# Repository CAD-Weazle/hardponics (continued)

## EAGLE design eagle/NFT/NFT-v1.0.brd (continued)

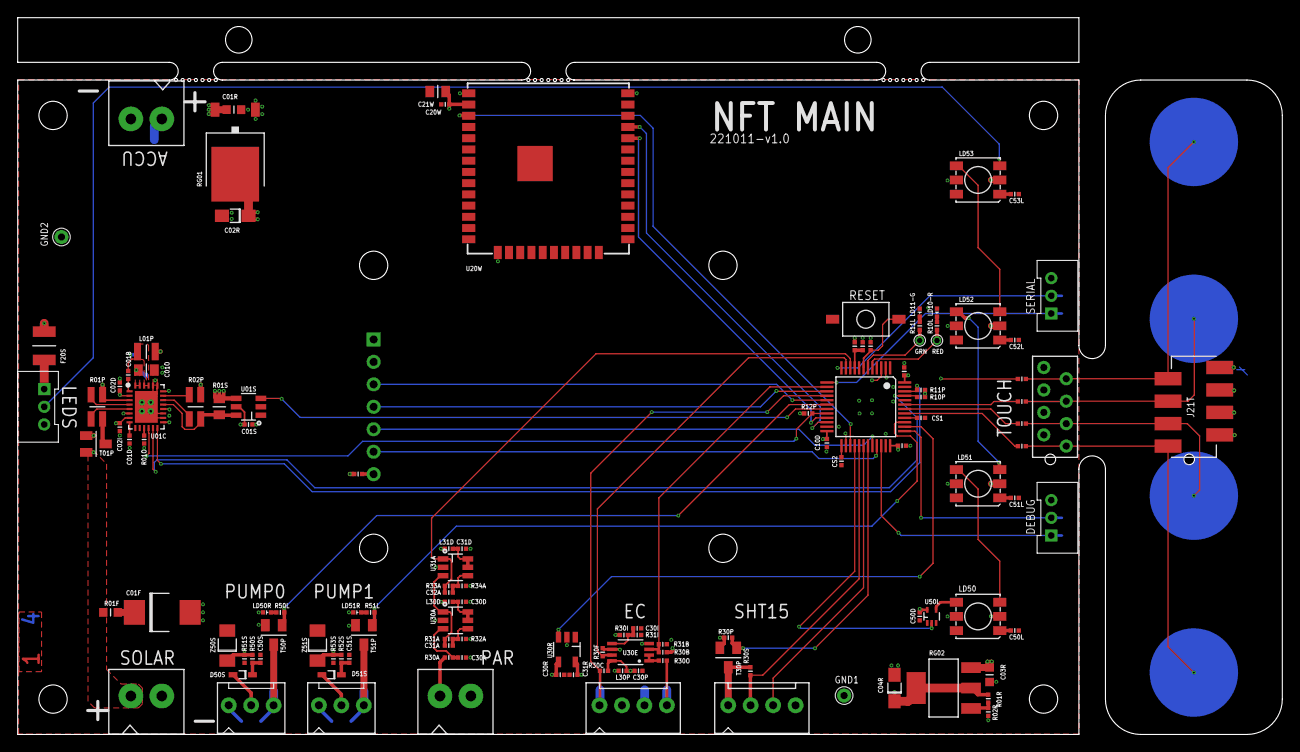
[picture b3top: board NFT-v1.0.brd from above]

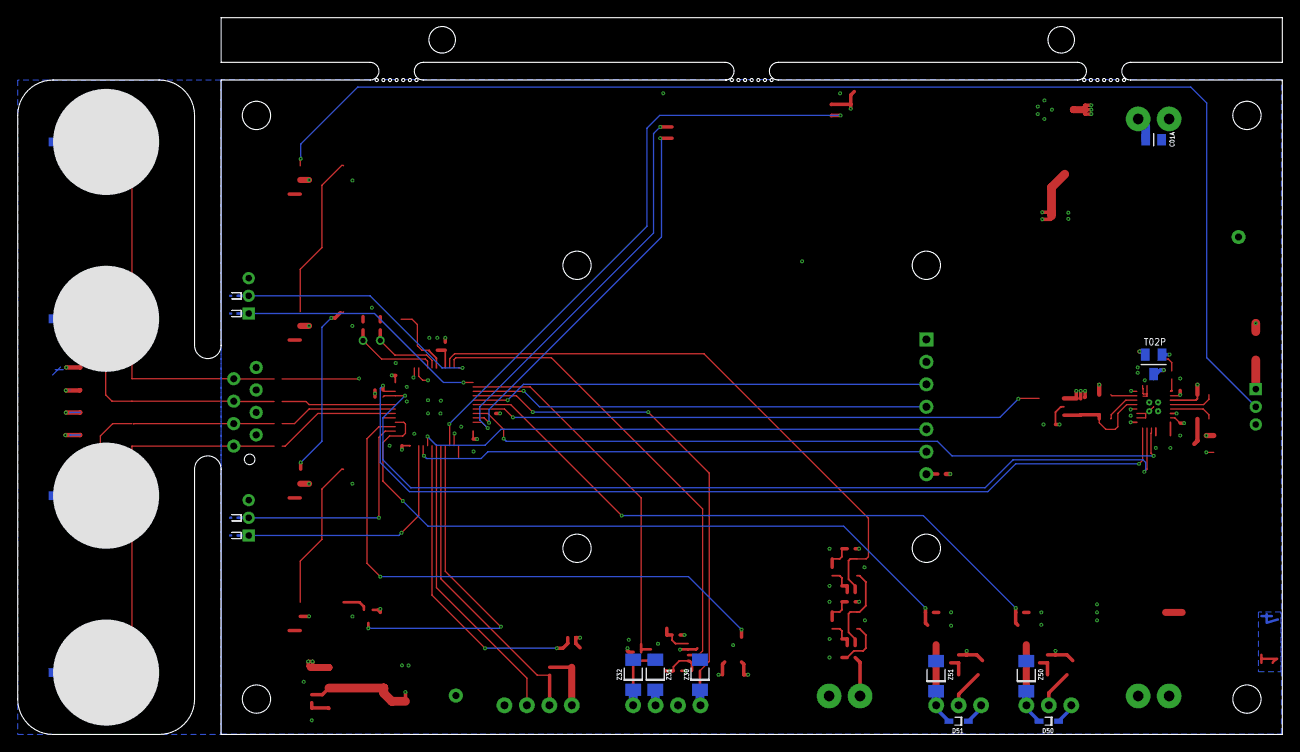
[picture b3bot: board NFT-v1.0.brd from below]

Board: 4 copper layers, 143.0 x 81.0 mm, 150 parts (17 on the bottom side), 99 nets.

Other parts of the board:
U$132, U$133, U$134: EC_MOUSEBITES
U$136, U$137: EC_TOOL-REGISTRATION

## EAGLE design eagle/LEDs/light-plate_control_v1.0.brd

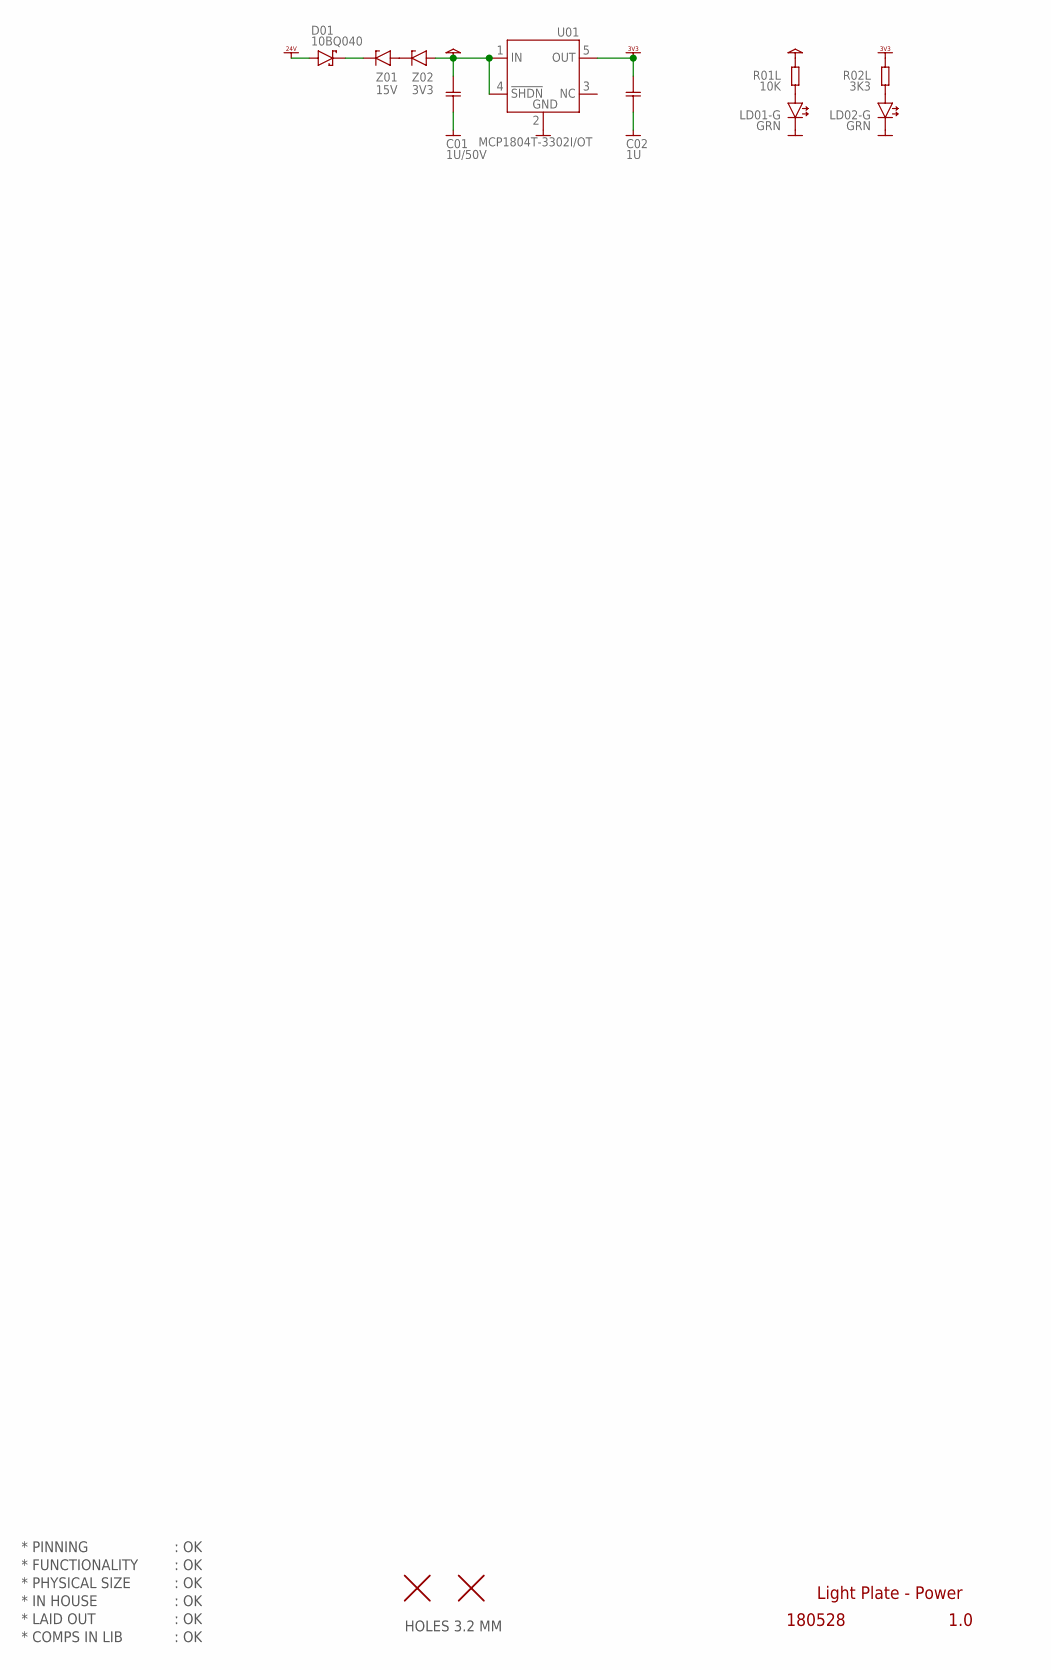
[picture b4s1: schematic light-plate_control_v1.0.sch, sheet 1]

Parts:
C01: 1U/50V; CAP0603
C02: 1U; CAP0603
D01: 10BQ040; DIODE_SMA
H2, H3: HOLE_NPTH_3.2MM
LD01-G, LD02-G: GRN; LED_SMD_0603
R01L: 10K; RES0603
R02L: 3K3; RES0603
U01: MCP1804T-3302I/OT; SOT23-5
Z01: 15V; ZENER_SOD80
Z02: 3V3; ZENER_SOD80

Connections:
GND: C01.2, C02.2, LD01-G.C, LD02-G.C, U01.2 (2.GND); also elsewhere on the board
unnamed: LD02-G.A, R02L.2
unnamed: LD01-G.A, R01L.2
unnamed: D01.C (-), Z01.2 (-)
unnamed: Z01.1 (+), Z02.2 (-)
VCC: C01.1, R01L.1, U01.1 (1.IN), U01.4 (4.SHDN), Z02.1 (+)
VDD_3V3: C02.1, R02L.1, U01.5 (5.OUT); also elsewhere on the board
VDD_24V: D01.A (+); also elsewhere on the board

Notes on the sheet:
* PINNING
* FUNCTIONALITY
* PHYSICAL SIZE
* LAID OUT
* COMPS IN LIB
* IN HOUSE
HOLES 3.2 MM
Light Plate - Power
180528
1.0
: OK

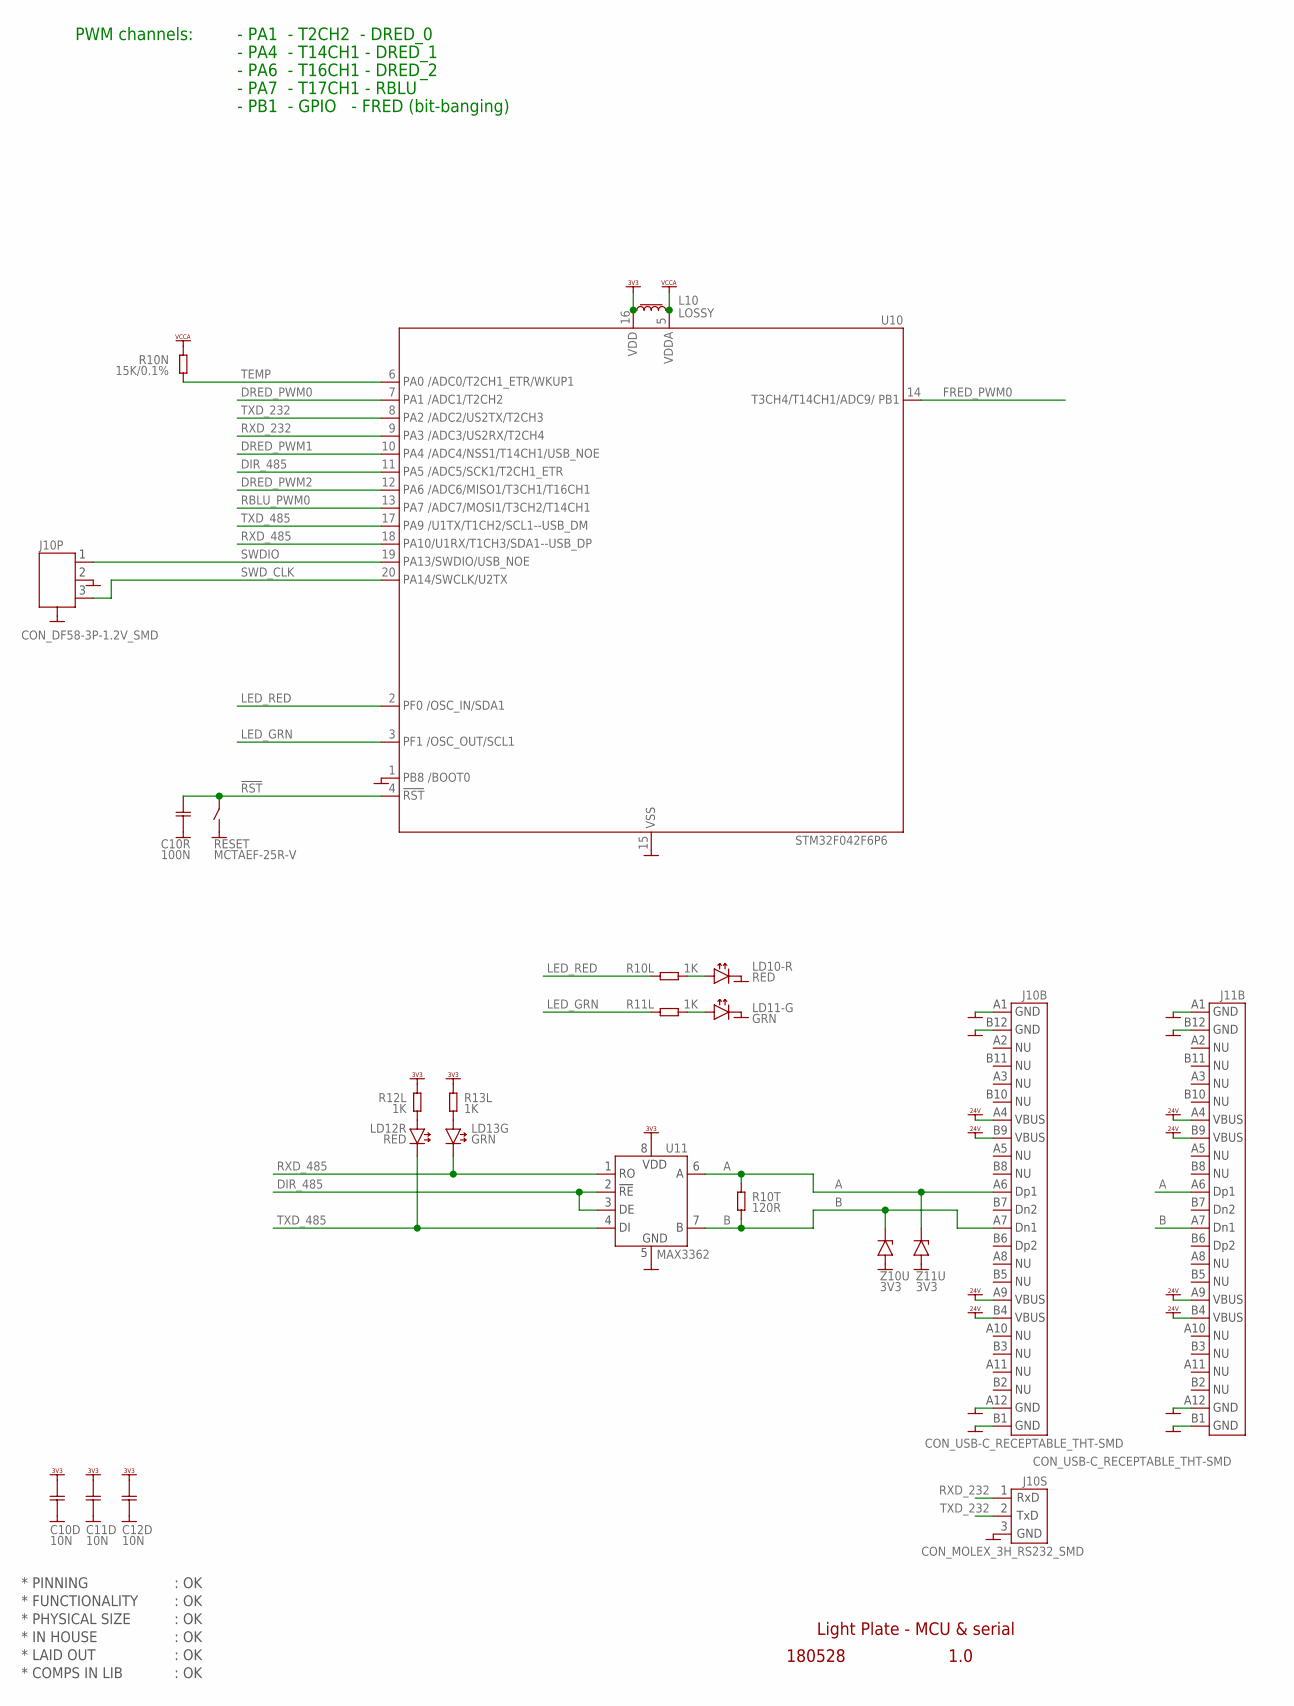
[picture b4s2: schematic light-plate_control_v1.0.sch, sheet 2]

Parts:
C10D, C11D, C12D: 10N; CAP0603
C10R: 100N; CAP0603
J10B, J11B: CON_USB-C_RECEPTABLE_THT-SMD
J10P: CON_DF58-3P-1.2V_SMD
J10S: CON_MOLEX_3H_RS232_SMD; CON_MOLEX_3H+SMD
L10: LOSSY; L_0603
LD10-R, LD12R: RED; LED_SMD_0603
LD11-G, LD13G: GRN; LED_SMD_0603
R10L, R11L, R12L, R13L: 1K; RES0603
R10N: 15K/0.1%; RES0603
R10T: 120R; RES0603
RESET: MCTAEF-25R-V; SWITCH_SMD_PBUTTON_2P
U10: STM32F042F6P6; TSSOP20
U11: MAX3362; SOT23-8
Z10U, Z11U: 3V3; ZENER_SOD80

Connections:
!RST: C10R.1, RESET.2 (3-4), U10.4 (4.!RST)
A: J10B.A6 (A6.DP1), J11B.A6 (A6.DP1), R10T.1, U11.6 (6.A), Z11U.2 (-)
B: J10B.A7 (A7.DN1), J11B.A7 (A7.DN1), R10T.2, U11.7 (7.B), Z10U.2 (-)
DIR_485: U10.11 (11.PA5), U11.2 (2.!RE), U11.3 (3.DE)
DRED_PWM0: U10.7 (7.PA1); also elsewhere on the board
DRED_PWM1: U10.10 (10.PA4); also elsewhere on the board
DRED_PWM2: U10.12 (12.PA6); also elsewhere on the board
FRED_PWM0: U10.14 (14.PB1); also elsewhere on the board
GND: C10D.2, C10R.2, C11D.2, C12D.2, J10B.A1 (A1.GND), J10B.A12 (A12.GND), J10B.B1 (B1.GND), J10B.B12 (B12.GND), J10P.2, J10P.GND1 (4), J10P.GND2 (4), J10S.3, J11B.A1 (A1.GND), J11B.A12 (A12.GND), J11B.B1 (B1.GND), J11B.B12 (B12.GND), LD10-R.C, LD11-G.C, RESET.1 (1-2), U10.1 (1.BOOT0), U10.15 (15.GND), U11.5 (5.GND), Z10U.1 (+), Z11U.1 (+); also elsewhere on the board
LED_GRN: R11L.1, U10.3 (3.OSC_OUT)
LED_RED: R10L.1, U10.2 (2.OSC_IN)
unnamed: LD11-G.A, R11L.2
unnamed: LD10-R.A, R10L.2
unnamed: LD13G.A, R13L.2
unnamed: LD12R.A, R12L.2
RBLU_PWM0: U10.13 (13.PA7); also elsewhere on the board
RXD_232: J10S.1, U10.9 (9.PA3)
RXD_485: LD13G.C, U10.18 (18.PA10), U11.1 (1.RO)
SWDIO: J10P.1, U10.19 (19.PA13)
SWD_CLK: J10P.3, U10.20 (20.PA14)
TEMP: R10N.1, U10.6 (6.PA0)
TXD_232: J10S.2, U10.8 (8.PA2)
TXD_485: LD12R.C, U10.17 (17.PA9), U11.4 (4.DI)
VCCA: L10.2, R10N.2, U10.5 (5.VDDA)
VDD_3V3: C10D.1, C11D.1, C12D.1, L10.1, R12L.1, R13L.1, U10.16 (16.VDD), U11.8 (8.VDD); also elsewhere on the board
VDD_24V: J10B.A4 (A4.VBUS), J10B.A9 (A9.VBUS), J10B.B4 (B4.VBUS), J10B.B9 (B9.VBUS), J11B.A4 (A4.VBUS), J11B.A9 (A9.VBUS), J11B.B4 (B4.VBUS), J11B.B9 (B9.VBUS); also elsewhere on the board

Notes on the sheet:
* PINNING
* FUNCTIONALITY
* PHYSICAL SIZE
* LAID OUT
* COMPS IN LIB
* IN HOUSE
: OK
Light Plate - MCU & serial
180528
1.0
PWM channels:
- PA1 - T2CH2 - DRED_0
- PA4 - T14CH1 - DRED_1
- PA6 - T16CH1 - DRED_2
- PA7 - T17CH1 - RBLU
- PB1 - GPIO - FRED (bit-banging)

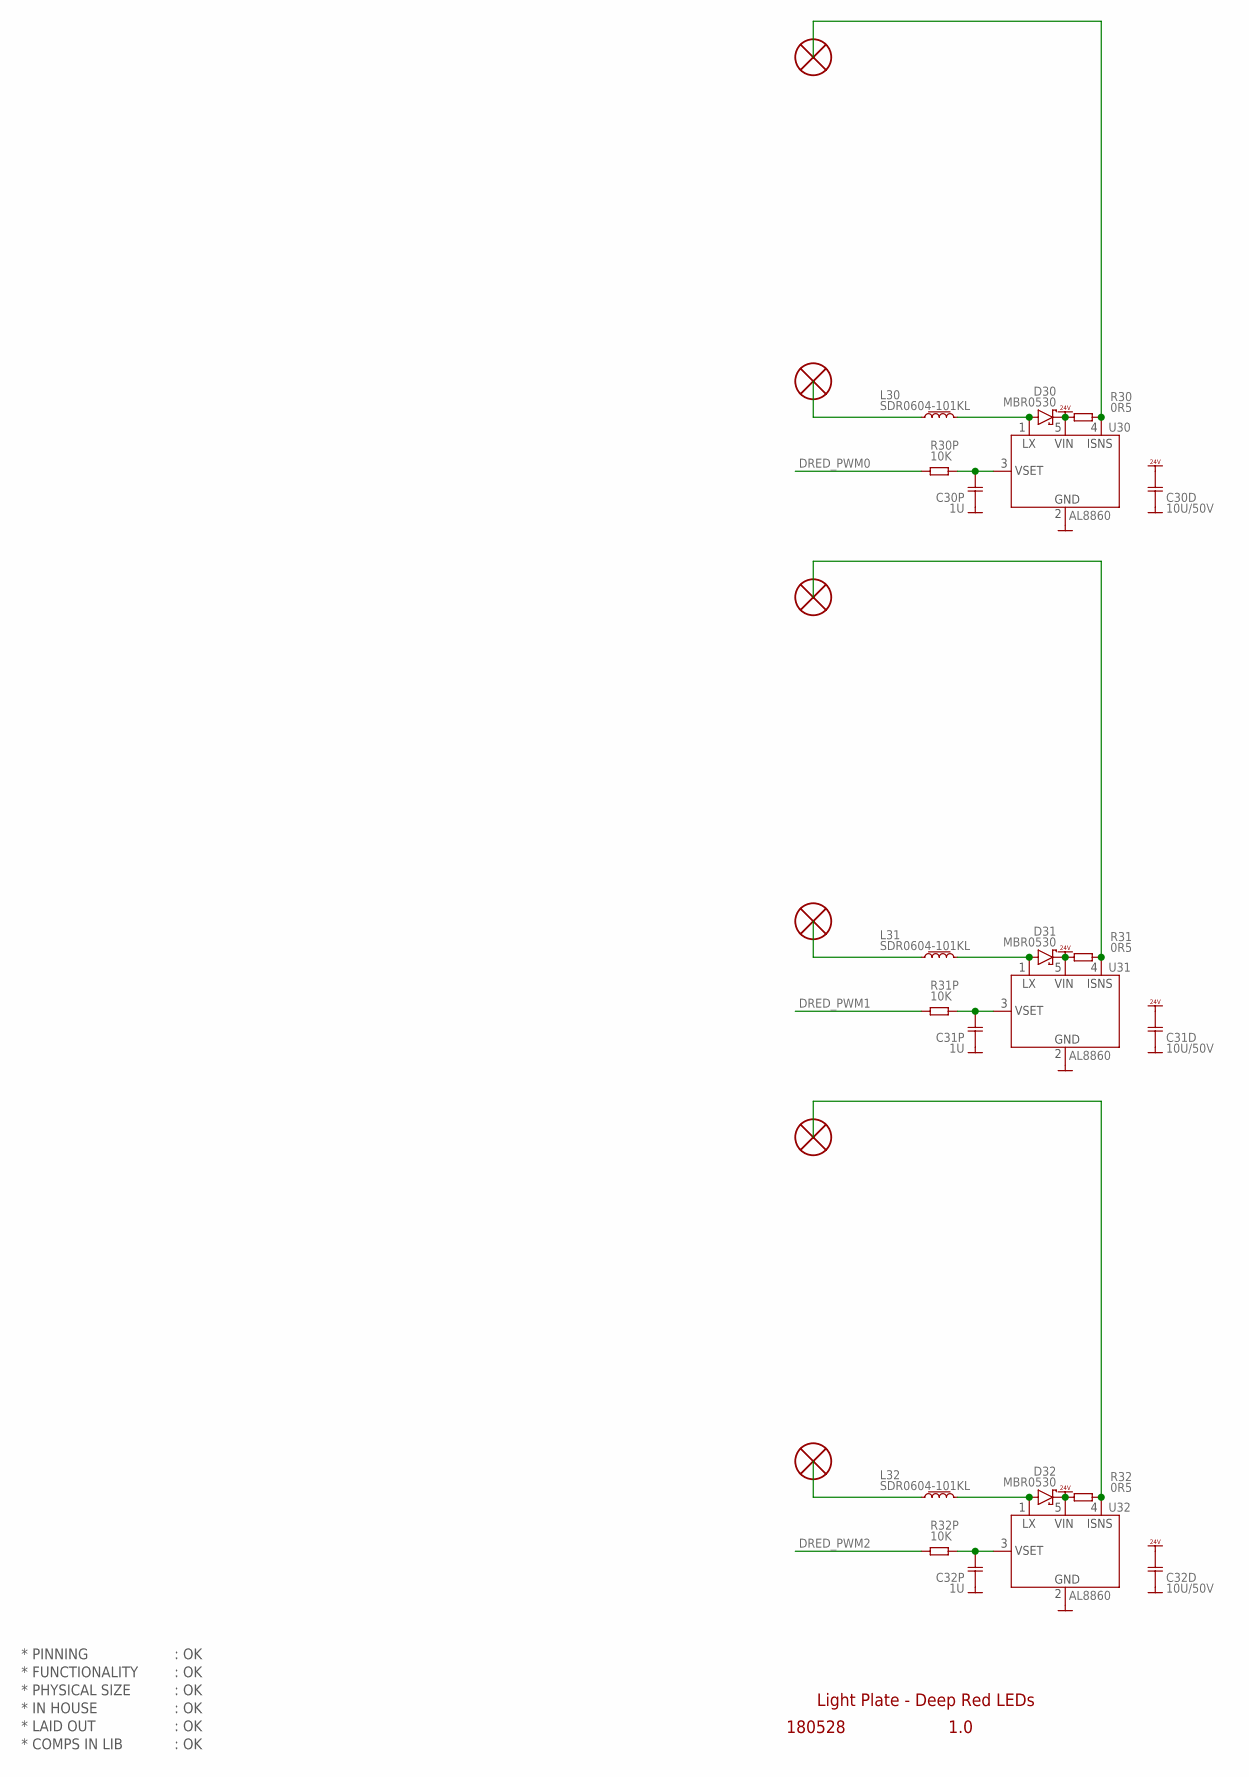
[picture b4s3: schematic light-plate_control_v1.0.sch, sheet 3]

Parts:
C30D, C31D, C32D: 10U/50V; CAP0603
C30P, C31P, C32P: 1U; CAP0603
D30, D31, D32: MBR0530; DIODE_SOD123
H5, H6, H7, H8, H9, H10: HOLE_PTH_1.0MM
L30, L31, L32: SDR0604-101KL; L_SDR0604
R30, R31, R32: 0R5; RES0603
R30P, R31P, R32P: 10K; RES0603
U30, U31, U32: AL8860; SOT23-5

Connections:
DRED_PWM0: R30P.1; also elsewhere on the board
DRED_PWM1: R31P.1; also elsewhere on the board
DRED_PWM2: R32P.1; also elsewhere on the board
GND: C30D.2, C30P.2, C31D.2, C31P.2, C32D.2, C32P.2, U30.2 (2.GND), U31.2 (2.GND), U32.2 (2.GND); also elsewhere on the board
unnamed: C30P.1, R30P.2, U30.3 (3.VSET)
unnamed: H5.1, L30.1
unnamed: H8.1, R31.2, U31.4 (4.ISENSE)
unnamed: D30.2 (+), L30.2, U30.1 (1.LX)
unnamed: H6.1, R30.2, U30.4 (4.ISENSE)
unnamed: H7.1, L31.1
unnamed: H10.1, R32.2, U32.4 (4.ISENSE)
unnamed: H9.1, L32.1
unnamed: D31.2 (+), L31.2, U31.1 (1.LX)
unnamed: C31P.1, R31P.2, U31.3 (3.VSET)
unnamed: D32.2 (+), L32.2, U32.1 (1.LX)
unnamed: C32P.1, R32P.2, U32.3 (3.VSET)
VDD_24V: C30D.1, C31D.1, C32D.1, D30.1- (-), D31.1- (-), D32.1- (-), R30.1, R31.1, R32.1, U30.5 (5.VIN), U31.5 (5.VIN), U32.5 (5.VIN); also elsewhere on the board

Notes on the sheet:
* PINNING
* FUNCTIONALITY
* PHYSICAL SIZE
* LAID OUT
* COMPS IN LIB
* IN HOUSE
: OK
Light Plate - Deep Red LEDs
1.0
180528

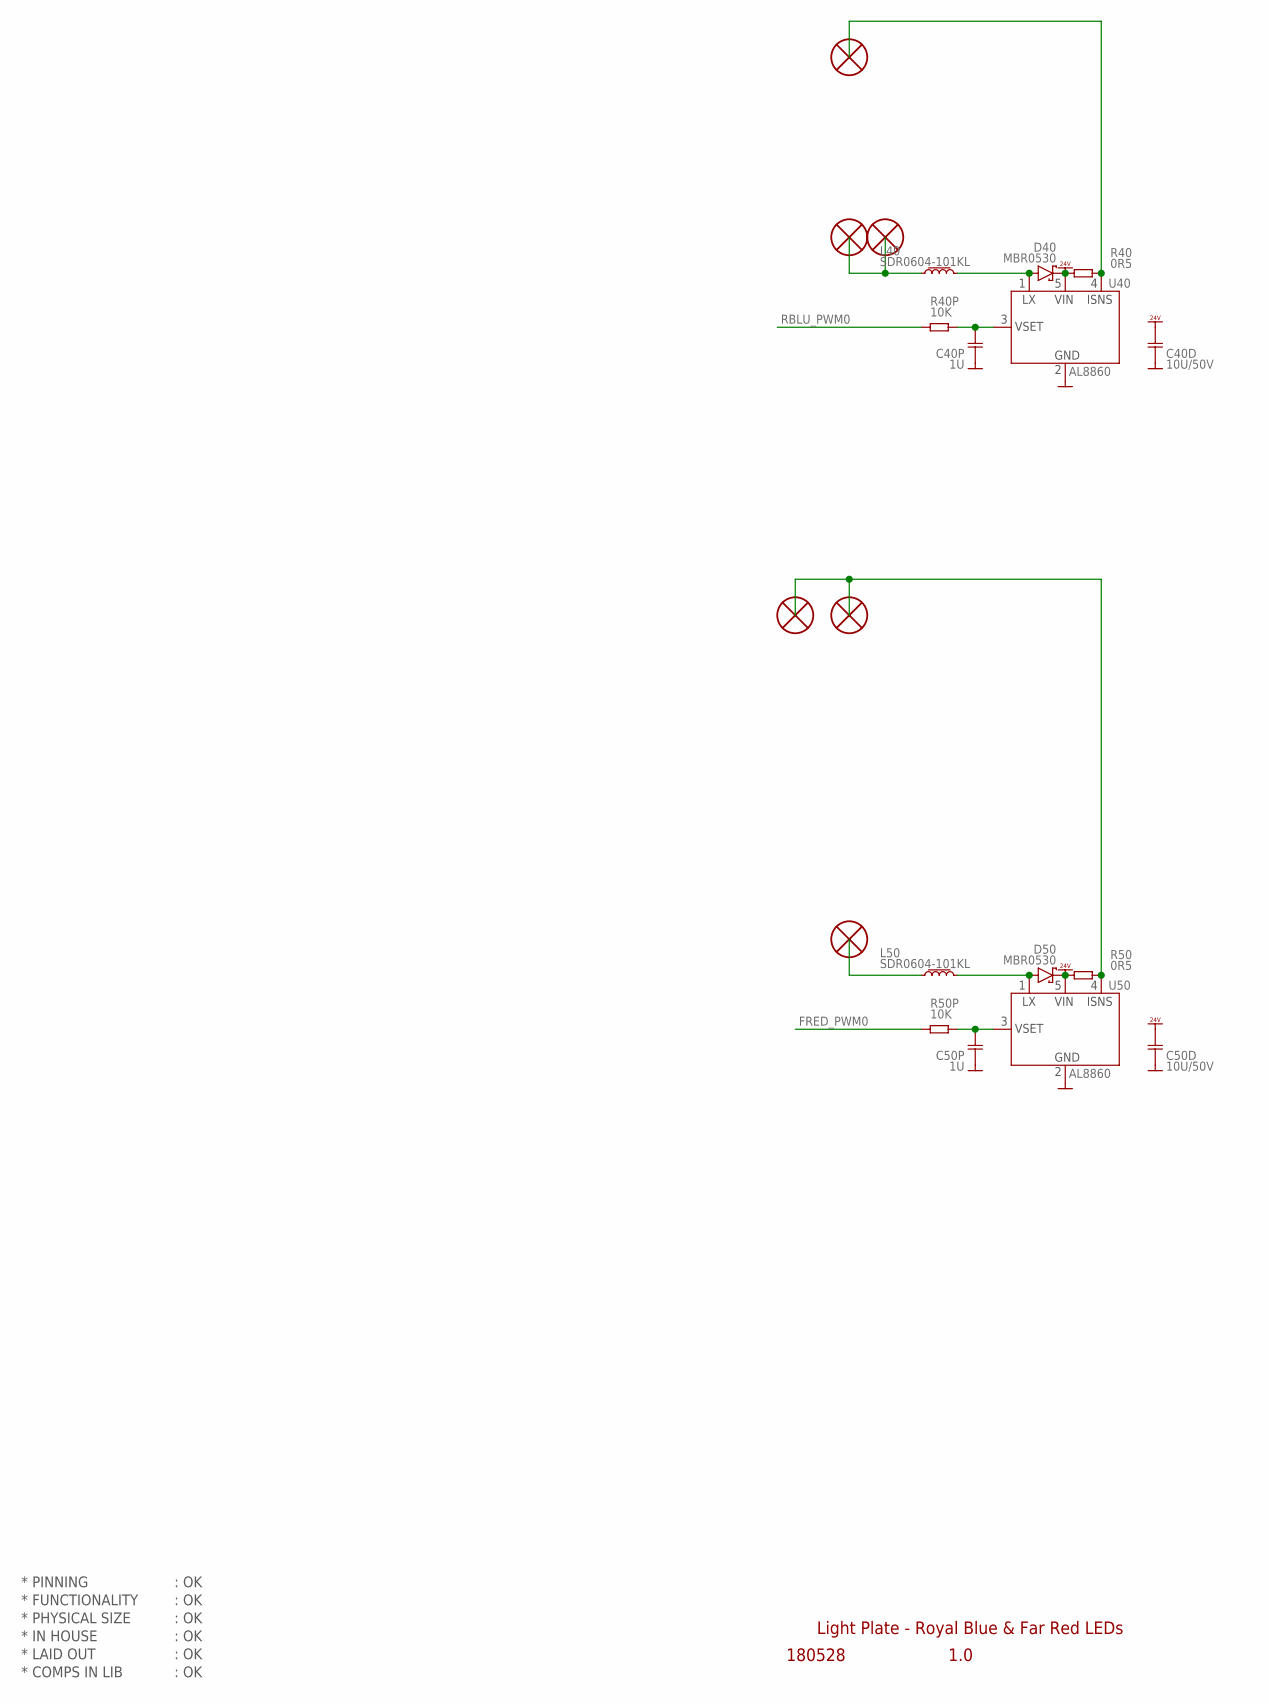
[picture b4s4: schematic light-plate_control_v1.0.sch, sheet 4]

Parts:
C40D, C50D: 10U/50V; CAP0603
C40P, C50P: 1U; CAP0603
D40, D50: MBR0530; DIODE_SOD123
H11, H12, H13, H14, H15, H16: HOLE_PTH_1.0MM
L40, L50: SDR0604-101KL; L_SDR0604
R40, R50: 0R5; RES0603
R40P, R50P: 10K; RES0603
U40, U50: AL8860; SOT23-5

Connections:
FRED_PWM0: R50P.1; also elsewhere on the board
GND: C40D.2, C40P.2, C50D.2, C50P.2, U40.2 (2.GND), U50.2 (2.GND); also elsewhere on the board
unnamed: H11.1, H15.1, L40.1
unnamed: H12.1, R40.2, U40.4 (4.ISENSE)
unnamed: H14.1, H16.1, R50.2, U50.4 (4.ISENSE)
unnamed: D50.2 (+), L50.2, U50.1 (1.LX)
unnamed: C50P.1, R50P.2, U50.3 (3.VSET)
unnamed: H13.1, L50.1
unnamed: D40.2 (+), L40.2, U40.1 (1.LX)
unnamed: C40P.1, R40P.2, U40.3 (3.VSET)
RBLU_PWM0: R40P.1; also elsewhere on the board
VDD_24V: C40D.1, C50D.1, D40.1- (-), D50.1- (-), R40.1, R50.1, U40.5 (5.VIN), U50.5 (5.VIN); also elsewhere on the board

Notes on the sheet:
* PINNING
* FUNCTIONALITY
* PHYSICAL SIZE
* LAID OUT
* COMPS IN LIB
* IN HOUSE
: OK
Light Plate - Royal Blue & Far Red LEDs
1.0
180528

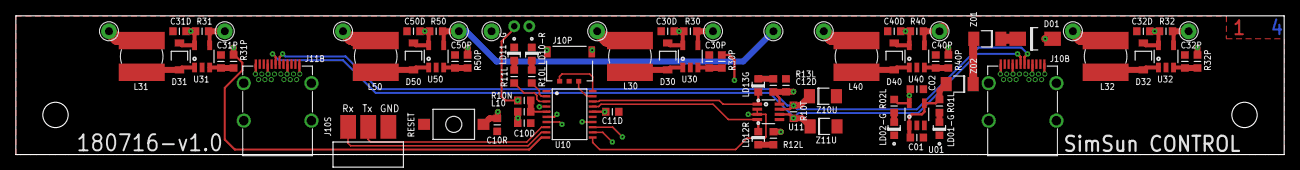
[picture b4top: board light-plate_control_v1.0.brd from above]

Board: 4 copper layers, 160.0 x 17.5 mm, 83 parts (0 on the bottom side), 51 nets.

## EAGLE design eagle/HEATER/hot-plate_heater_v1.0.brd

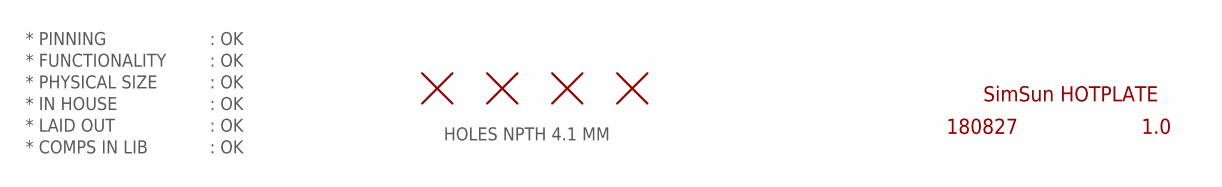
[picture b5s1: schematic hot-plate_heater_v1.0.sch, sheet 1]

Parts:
H1, H2, H3, H4: HOLE_NPTH_4.1MM

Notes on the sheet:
* PINNING
* FUNCTIONALITY
* PHYSICAL SIZE
* LAID OUT
* COMPS IN LIB
* IN HOUSE
HOLES NPTH 4.1 MM
SimSun HOTPLATE
180827
1.0
: OK

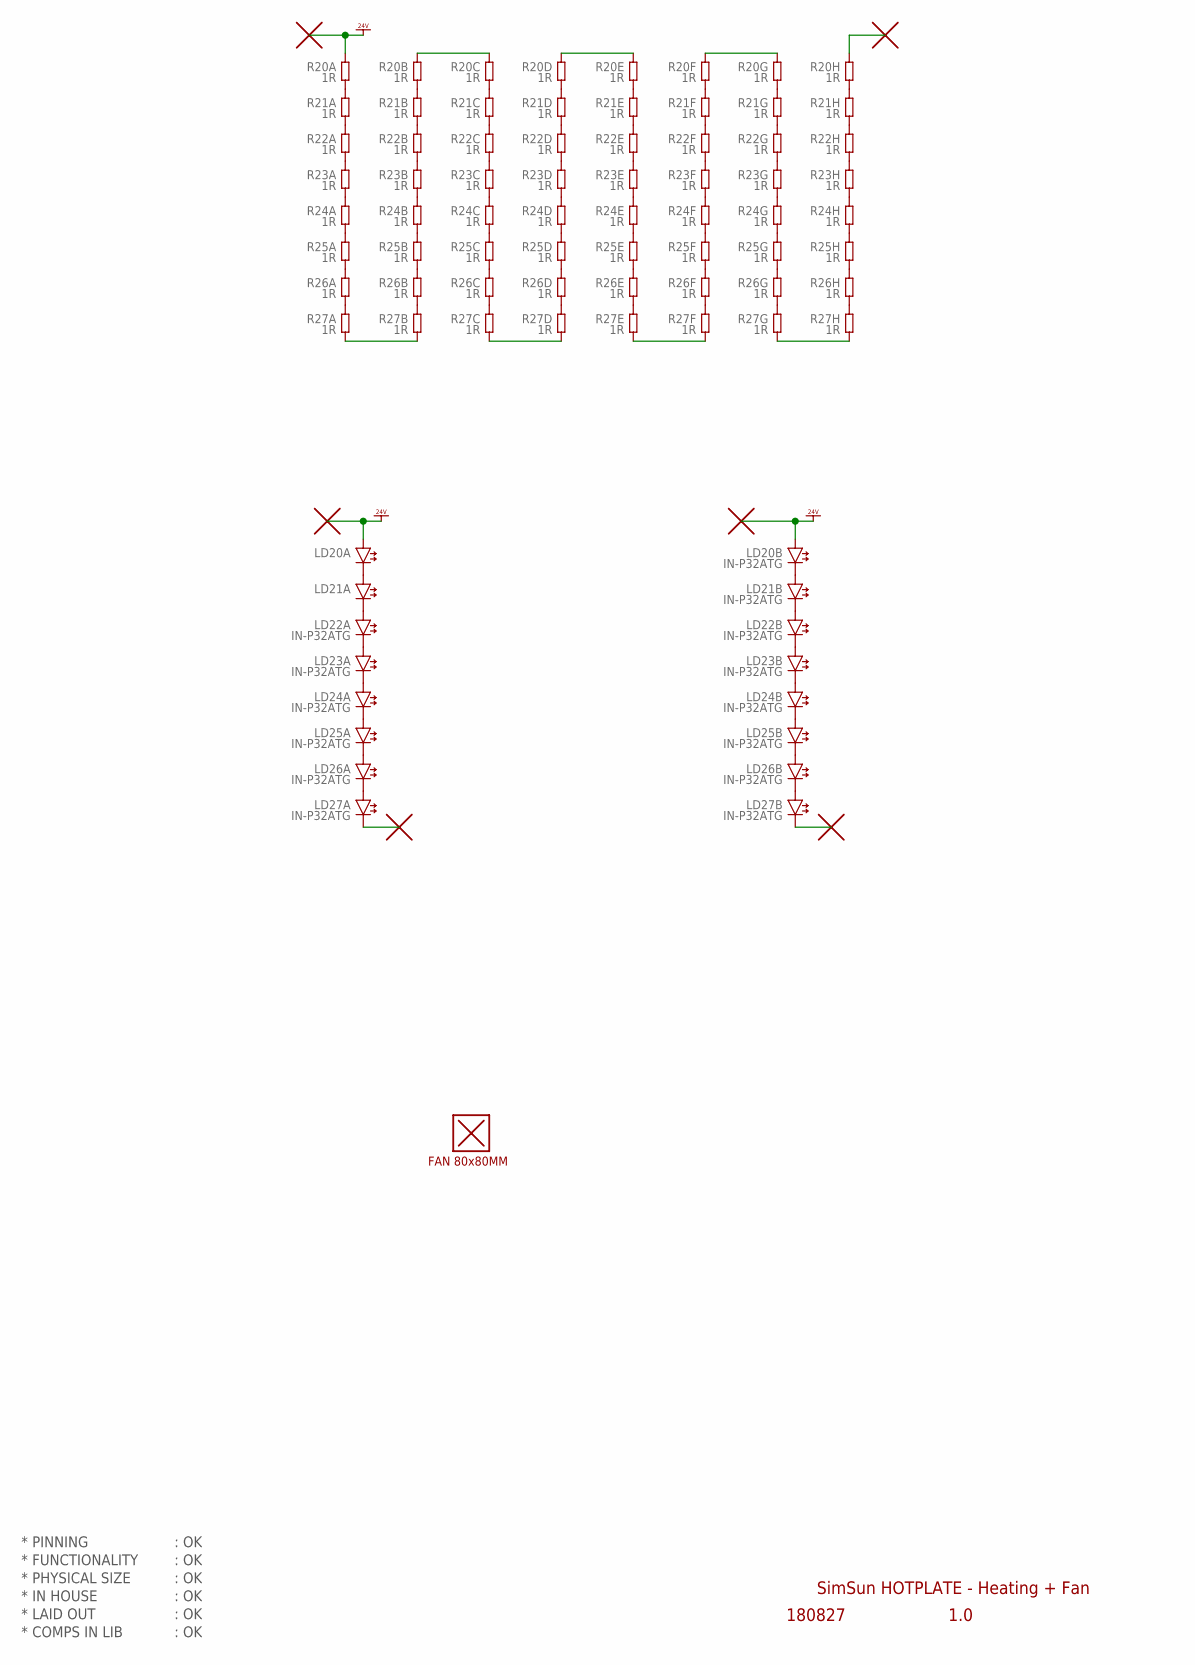
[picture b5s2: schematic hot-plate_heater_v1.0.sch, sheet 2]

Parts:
H9: FAN_80X80MM_SANYO_SANACE80
H18, H19, H20, H21, H22, H23: PAD_ROUND_3.2MM
LD20A, LD20B, LD21A, LD21B, LD22A, LD22B, LD23A, LD23B, LD24A, LD24B, LD25A, LD25B, LD26A, LD26B, LD27A, LD27B: IN-P32ATG; LED_SMD_PLCC2
R20A, R20B, R20C, R20D, R20E, R20F, R20G, R20H, R21A, R21B, R21C, R21D, R21E, R21F, R21G, R21H, R22A, R22B, R22C, R22D, R22E, R22F, R22G, R22H, R23A, R23B, R23C, R23D, R23E, R23F, R23G, R23H, R24A, R24B, R24C, R24D, R24E, R24F, R24G, R24H, R25A, R25B, R25C, R25D, R25E, R25F, R25G, R25H, R26A, R26B, R26C, R26D, R26E, R26F, R26G, R26H, R27A, R27B, R27C, R27D, R27E, R27F, R27G, R27H: 1R; RES2512

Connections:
unnamed: H19.P, R20H.1
unnamed: R20A.2, R21A.1
unnamed: R21A.2, R22A.1
unnamed: R22A.2, R23A.1
unnamed: R23A.2, R24A.1
unnamed: R24A.2, R25A.1
unnamed: R25A.2, R26A.1
unnamed: R26A.2, R27A.1
unnamed: R20B.2, R21B.1
unnamed: R21B.2, R22B.1
unnamed: R22B.2, R23B.1
unnamed: R23B.2, R24B.1
unnamed: R24B.2, R25B.1
unnamed: R25B.2, R26B.1
unnamed: R26B.2, R27B.1
unnamed: R27A.2, R27B.2
unnamed: R20C.2, R21C.1
unnamed: R21C.2, R22C.1
unnamed: R22C.2, R23C.1
unnamed: R23C.2, R24C.1
unnamed: R24C.2, R25C.1
unnamed: R25C.2, R26C.1
unnamed: R26C.2, R27C.1
unnamed: R20B.1, R20C.1
unnamed: R20D.2, R21D.1
unnamed: R21D.2, R22D.1
unnamed: R22D.2, R23D.1
unnamed: R23D.2, R24D.1
unnamed: R24D.2, R25D.1
unnamed: R25D.2, R26D.1
unnamed: R26D.2, R27D.1
unnamed: R27C.2, R27D.2
unnamed: R20E.2, R21E.1
unnamed: R21E.2, R22E.1
unnamed: R22E.2, R23E.1
unnamed: R23E.2, R24E.1
unnamed: R24E.2, R25E.1
unnamed: R25E.2, R26E.1
unnamed: R26E.2, R27E.1
unnamed: R20D.1, R20E.1
unnamed: R20F.2, R21F.1
unnamed: R21F.2, R22F.1
unnamed: R22F.2, R23F.1
unnamed: R23F.2, R24F.1
unnamed: R24F.2, R25F.1
unnamed: R25F.2, R26F.1
unnamed: R26F.2, R27F.1
unnamed: R27E.2, R27F.2
unnamed: R20G.2, R21G.1
unnamed: R21G.2, R22G.1
unnamed: R22G.2, R23G.1
unnamed: R23G.2, R24G.1
unnamed: R24G.2, R25G.1
unnamed: R25G.2, R26G.1
unnamed: R26G.2, R27G.1
unnamed: R20F.1, R20G.1
unnamed: R20H.2, R21H.1
unnamed: R21H.2, R22H.1
unnamed: R22H.2, R23H.1
unnamed: R23H.2, R24H.1
unnamed: R24H.2, R25H.1
unnamed: R25H.2, R26H.1
unnamed: R26H.2, R27H.1
unnamed: R27G.2, R27H.2
unnamed: LD20A.C (-), LD21A.A (+)
unnamed: LD21A.C (-), LD22A.A (+)
unnamed: LD22A.C (-), LD23A.A (+)
unnamed: LD23A.C (-), LD24A.A (+)
unnamed: LD24A.C (-), LD25A.A (+)
unnamed: LD25A.C (-), LD26A.A (+)
unnamed: LD20B.C (-), LD21B.A (+)
unnamed: LD21B.C (-), LD22B.A (+)
unnamed: LD22B.C (-), LD23B.A (+)
unnamed: LD23B.C (-), LD24B.A (+)
unnamed: LD24B.C (-), LD25B.A (+)
unnamed: LD25B.C (-), LD26B.A (+)
unnamed: LD26A.C (-), LD27A.A (+)
unnamed: LD26B.C (-), LD27B.A (+)
unnamed: H23.P, LD27B.C (-)
unnamed: H22.P, LD27A.C (-)
VDD_24V: H18.P, H20.P, H21.P, LD20A.A (+), LD20B.A (+), R20A.1

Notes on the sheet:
* PINNING
* FUNCTIONALITY
* PHYSICAL SIZE
* LAID OUT
* COMPS IN LIB
* IN HOUSE
: OK
SimSun HOTPLATE - Heating + Fan
1.0
180827

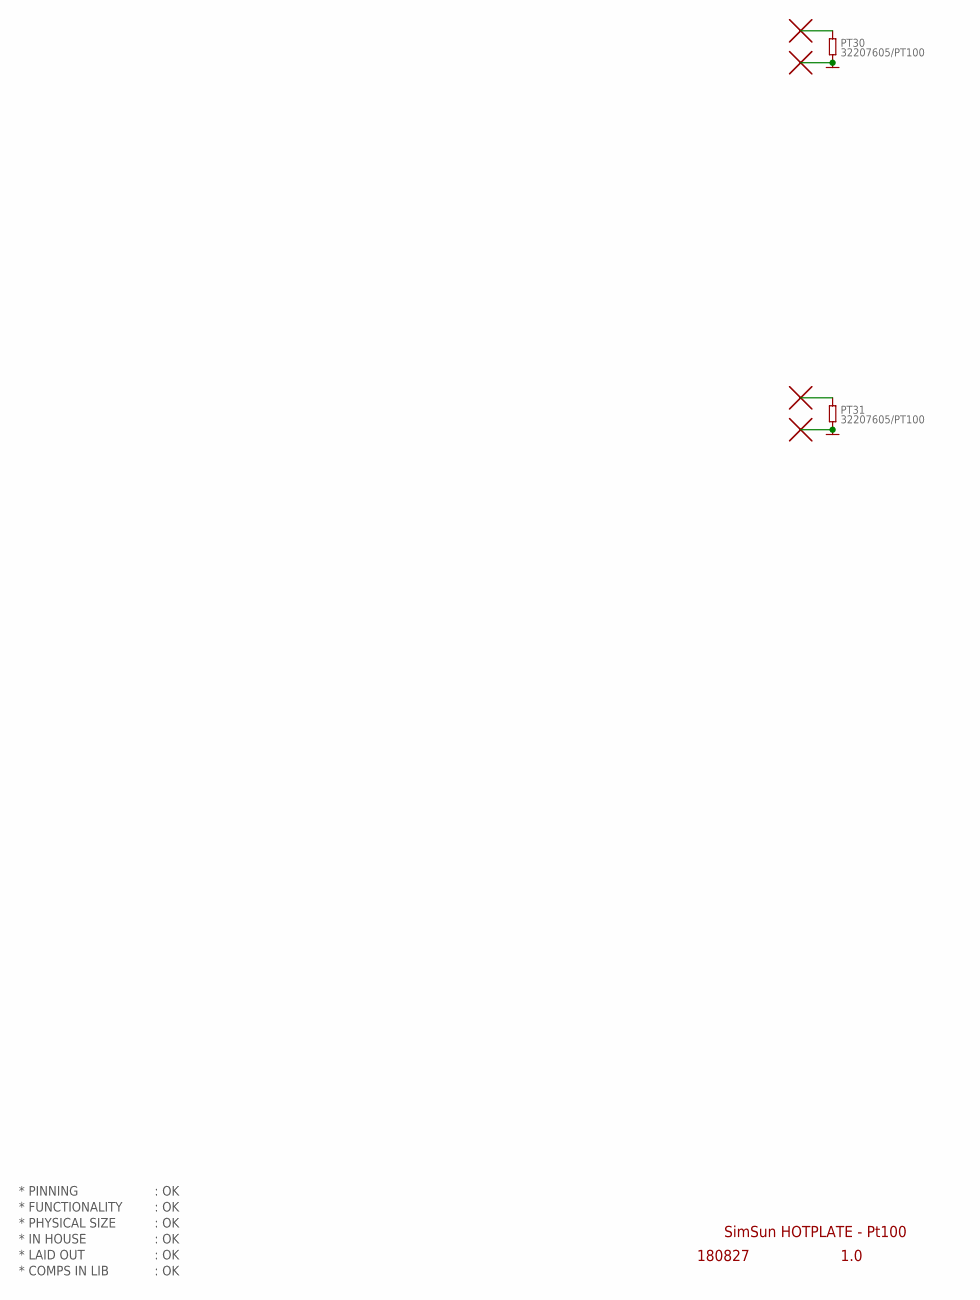
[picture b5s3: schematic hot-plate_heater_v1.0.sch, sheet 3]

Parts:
H24, H25, H26, H27: PAD_ROUND_3.2MM
PT30, PT31: 32207605/PT100; RES0805

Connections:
GND: H25.P, H27.P, PT30.2, PT31.2
RTD30: H24.P, PT30.1
RTD31: H26.P, PT31.1

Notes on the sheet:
* PINNING
* FUNCTIONALITY
* PHYSICAL SIZE
* LAID OUT
* COMPS IN LIB
* IN HOUSE
: OK
1.0
180827
SimSun HOTPLATE - Pt100

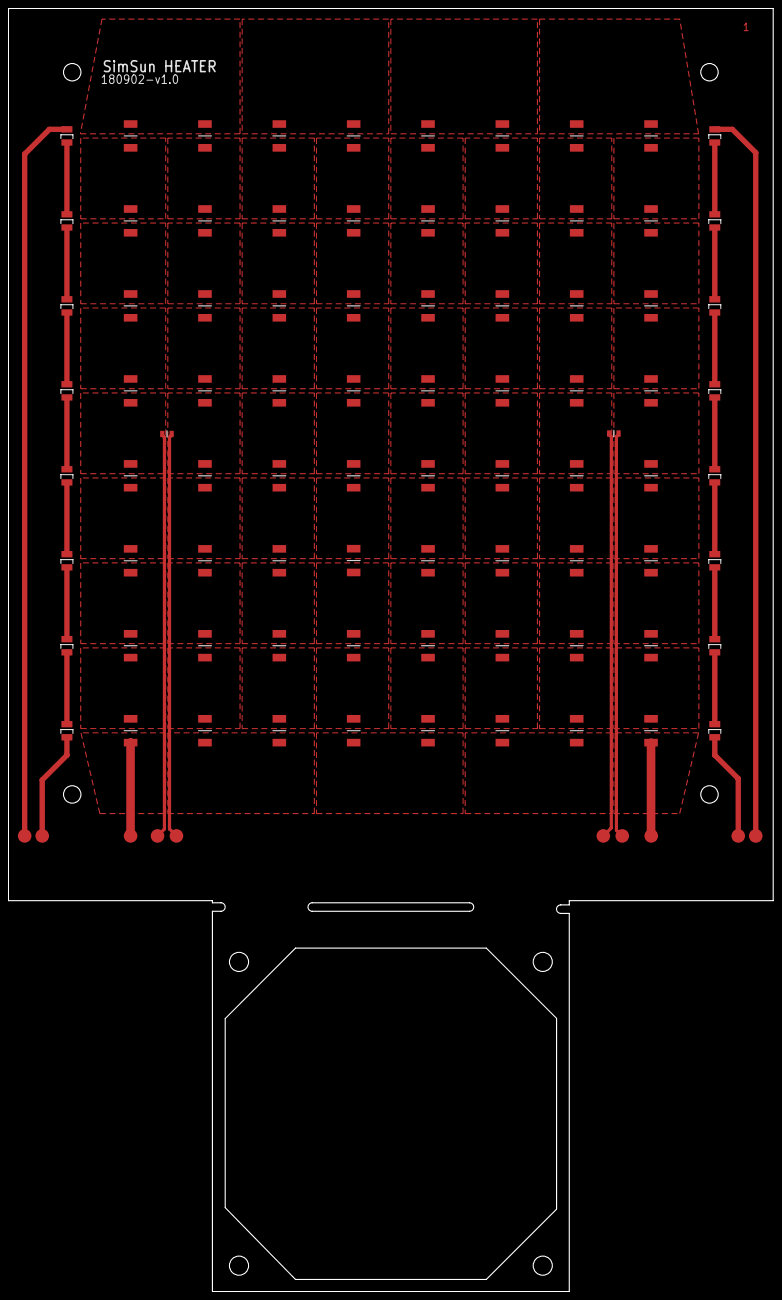
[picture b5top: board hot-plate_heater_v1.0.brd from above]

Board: 1 copper layer, 180.0 x 302.0 mm, 97 parts (0 on the bottom side), 84 nets.

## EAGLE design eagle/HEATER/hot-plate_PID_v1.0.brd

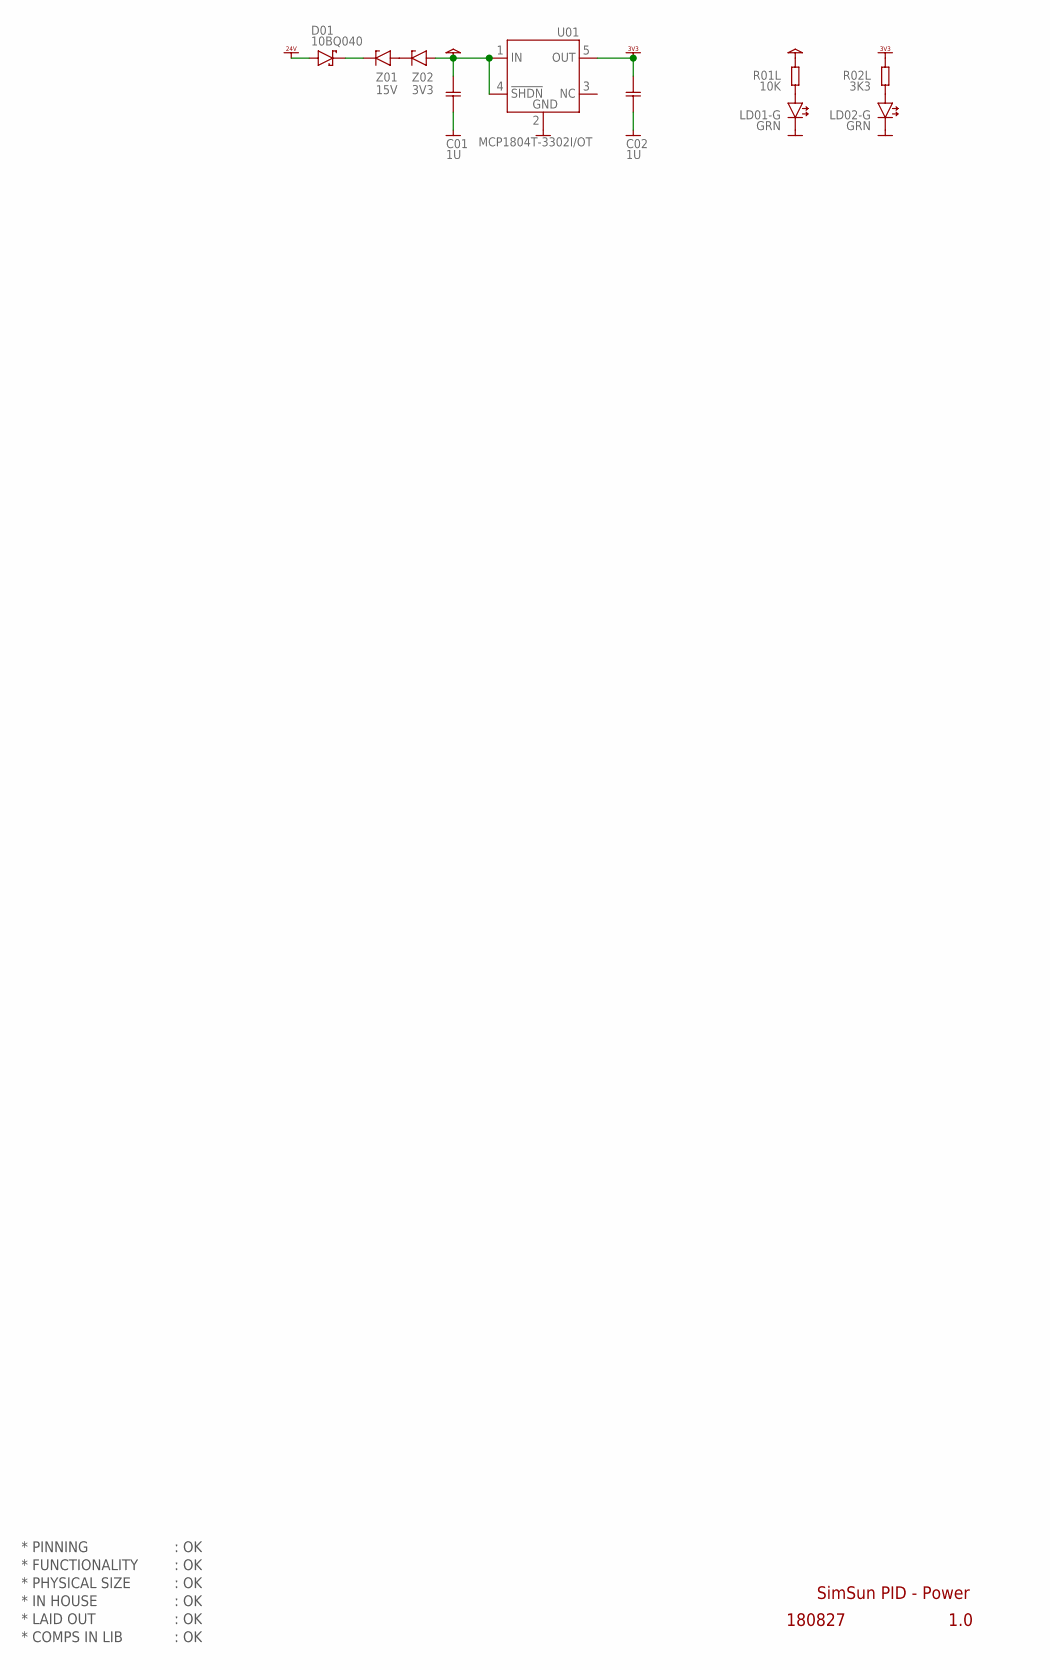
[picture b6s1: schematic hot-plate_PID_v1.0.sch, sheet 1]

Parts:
C01, C02: 1U; CAP0603
D01: 10BQ040; DIODE_SMA
LD01-G, LD02-G: GRN; LED_SMD_0603
R01L: 10K; RES0603
R02L: 3K3; RES0603
U01: MCP1804T-3302I/OT; SOT23-5
Z01: 15V; ZENER_SOD80
Z02: 3V3; ZENER_SOD80

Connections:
GND: C01.2, C02.2, LD01-G.C, LD02-G.C, U01.2 (2.GND); also elsewhere on the board
unnamed: LD02-G.A, R02L.2
unnamed: LD01-G.A, R01L.2
unnamed: D01.C (-), Z01.2 (-)
unnamed: Z01.1 (+), Z02.2 (-)
VCC: C01.1, R01L.1, U01.1 (1.IN), U01.4 (4.SHDN), Z02.1 (+)
VDD_3V3: C02.1, R02L.1, U01.5 (5.OUT); also elsewhere on the board
VDD_24V: D01.A (+); also elsewhere on the board

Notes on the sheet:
* PINNING
* FUNCTIONALITY
* PHYSICAL SIZE
* LAID OUT
* COMPS IN LIB
* IN HOUSE
SimSun PID - Power
180827
1.0
: OK
